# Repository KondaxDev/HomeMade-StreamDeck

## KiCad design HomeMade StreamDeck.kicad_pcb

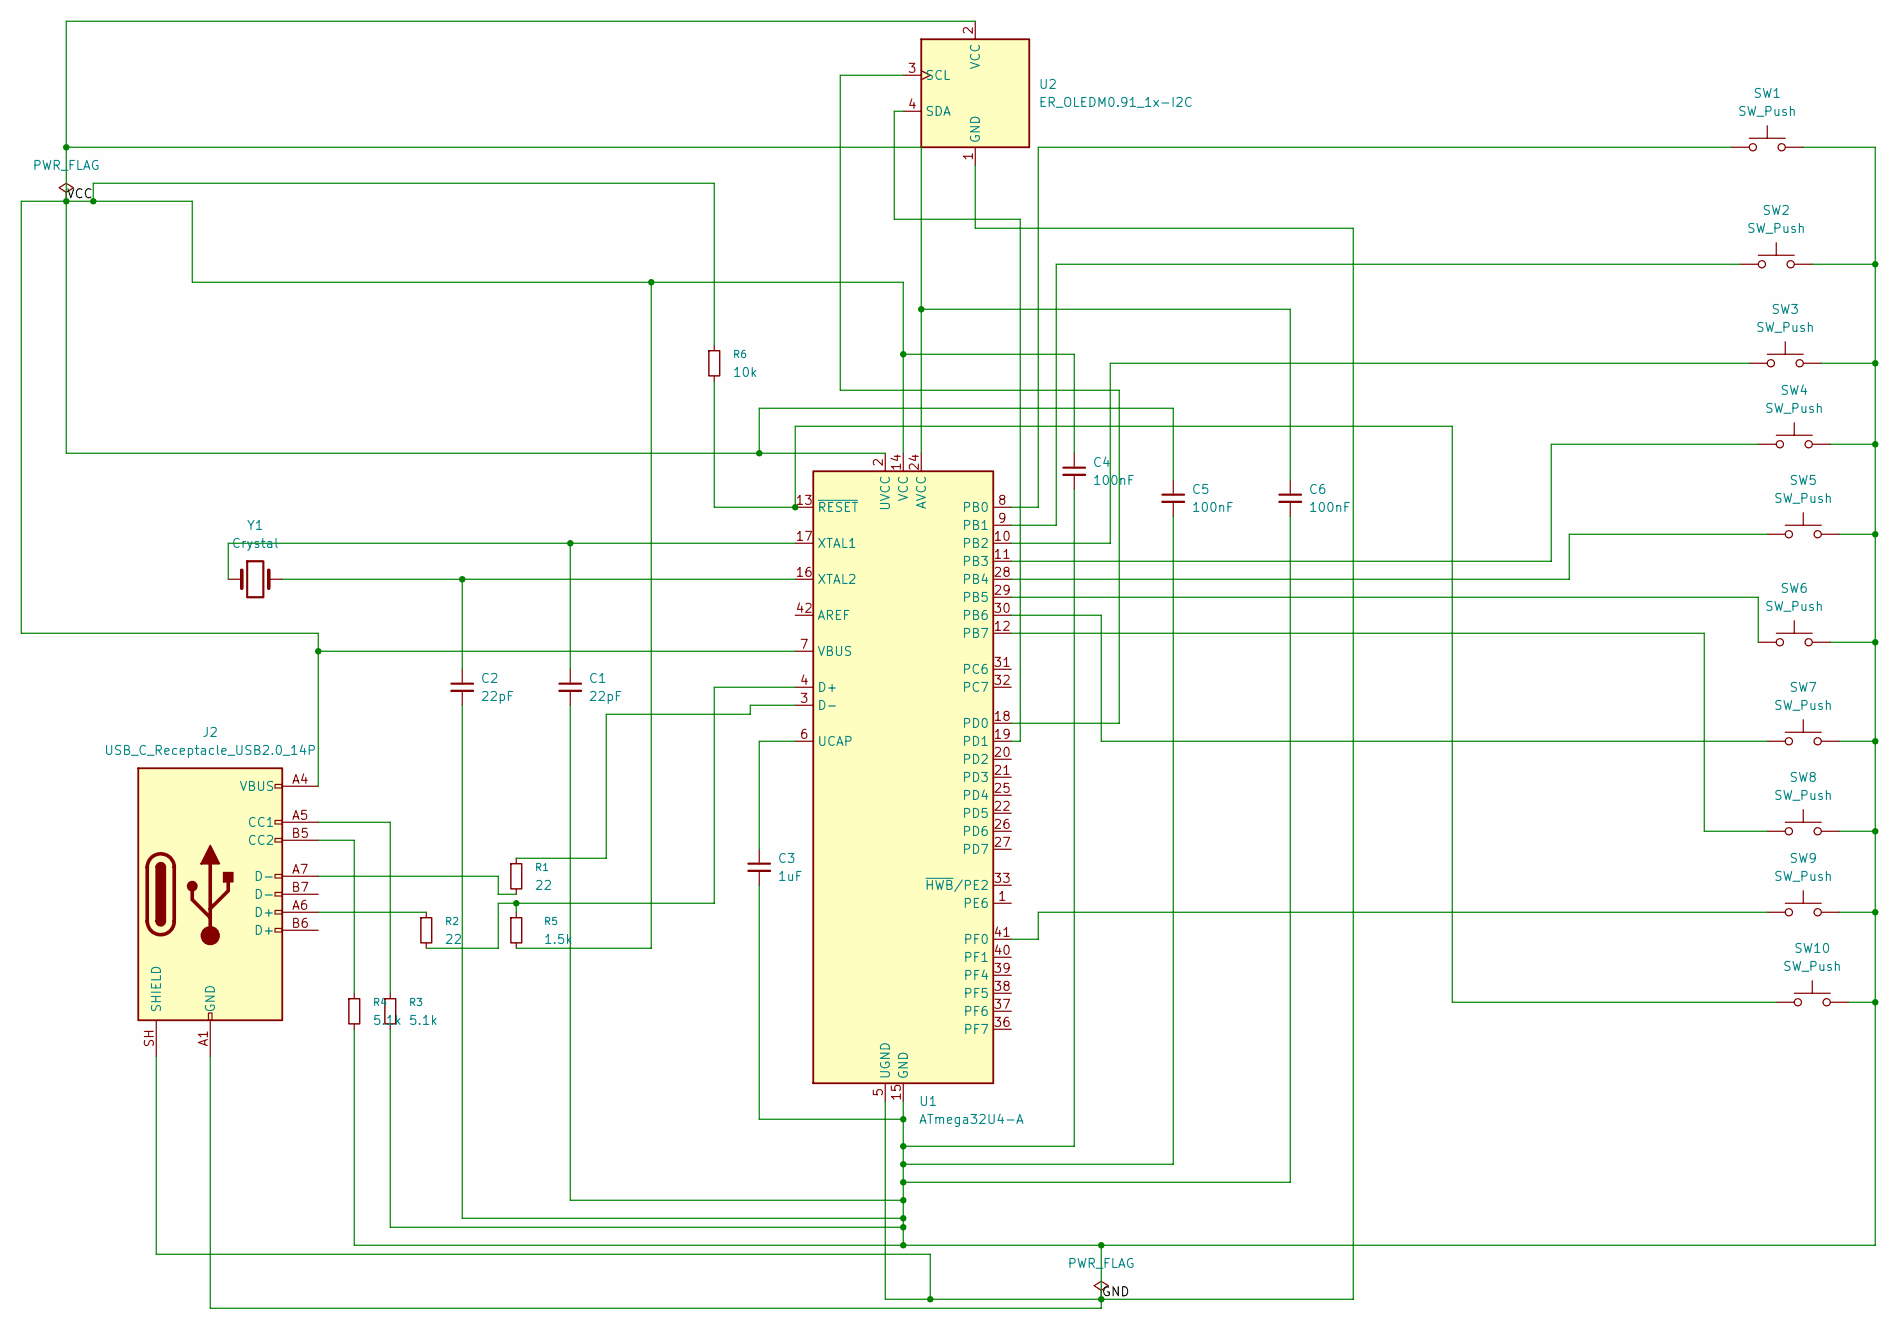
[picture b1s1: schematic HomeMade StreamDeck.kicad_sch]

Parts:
C1, C2: 22pF; C_0805_2012Metric
C3: 1uF; C_0805_2012Metric
C4, C5, C6: 100nF; C_0805_2012Metric
J2: USB_C_Receptacle_USB2.0_14P; USB_C_Receptacle_HCTL_HC-TYPE-C-16P-01A
R1, R2: 22; R_0805_2012Metric
R3, R4: 5.1k; R_0805_2012Metric
R5: 1.5k; R_0805_2012Metric
R6: 10k; R_0805_2012Metric
SW1, SW2, SW3, SW4, SW5, SW6, SW7, SW8, SW9, SW10: SW_Push; SW_PUSH_6mm
U1: ATmega32U4-A; TQFP-44_10x10mm_P0.8mm
U2: ER_OLEDM0.91_1x-I2C
Y1: Crystal; Crystal_SMD_HC49-SD

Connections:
/GND: C1.2, C2.2, C3.2, C4.2, C5.2, C6.2, J2.A1 (GND), J2.A12 (GND), J2.B1 (GND), J2.B12 (GND), J2.SH (SHIELD), R3.2, R4.2, SW1.2, SW2.2, SW3.2, SW4.2, SW5.2, SW6.2, SW7.2, SW8.2, SW9.2, SW10.2, U1.5 (UGND), U1.15 (GND), U1.23 (GND), U1.35 (GND), U1.43 (GND), U2.1 (GND)
/VCC: C4.1, C5.1, C6.1, J2.A4 (VBUS), J2.A9 (VBUS), J2.B4 (VBUS), J2.B9 (VBUS), R5.2, R6.1, U1.2 (UVCC), U1.7 (VBUS), U1.14 (VCC), U1.24 (AVCC), U1.34 (VCC), U1.44 (AVCC), U2.2 (VCC)
unnamed: J2.A5 (CC1), R3.1
unnamed: J2.B5 (CC2), R4.1
unnamed: J2.A6 (D+), R2.1
unnamed: J2.A7 (D-), R1.2
unnamed: R2.2, R5.1, U1.4 (D+)
unnamed: R1.1, U1.3 (D-)
unnamed: SW1.1, U1.8 (PB0)
unnamed: SW2.1, U1.9 (PB1)
unnamed: SW3.1, U1.10 (PB2)
unnamed: SW4.1, U1.11 (PB3)
unnamed: SW5.1, U1.28 (PB4)
unnamed: SW6.1, U1.29 (PB5)
unnamed: SW7.1, U1.30 (PB6)
unnamed: SW8.1, U1.12 (PB7)
unnamed: U1.18 (PD0), U2.3 (SCL)
unnamed: U1.19 (PD1), U2.4 (SDA)
unnamed: SW9.1, U1.41 (PF0)
unnamed: C3.1, U1.6 (UCAP)
unnamed: C1.1, U1.17 (XTAL1), Y1.1
unnamed: C2.1, U1.16 (XTAL2), Y1.2
unnamed: R6.2, SW10.1, U1.13 (~RESET)

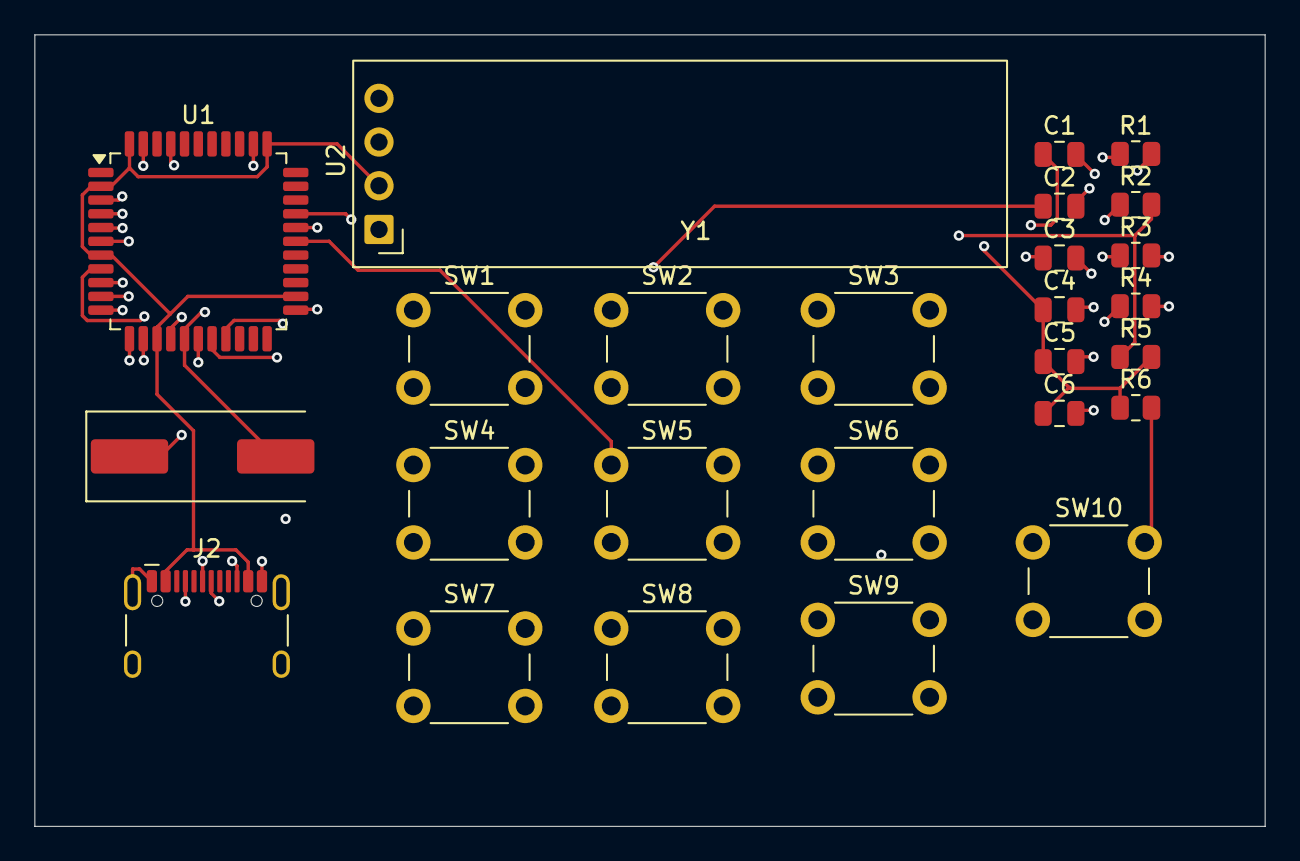
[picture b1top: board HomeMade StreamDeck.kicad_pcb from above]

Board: 4 copper layers, 71.5 x 46.0 mm, 26 parts (0 on the bottom side), 23 nets.
